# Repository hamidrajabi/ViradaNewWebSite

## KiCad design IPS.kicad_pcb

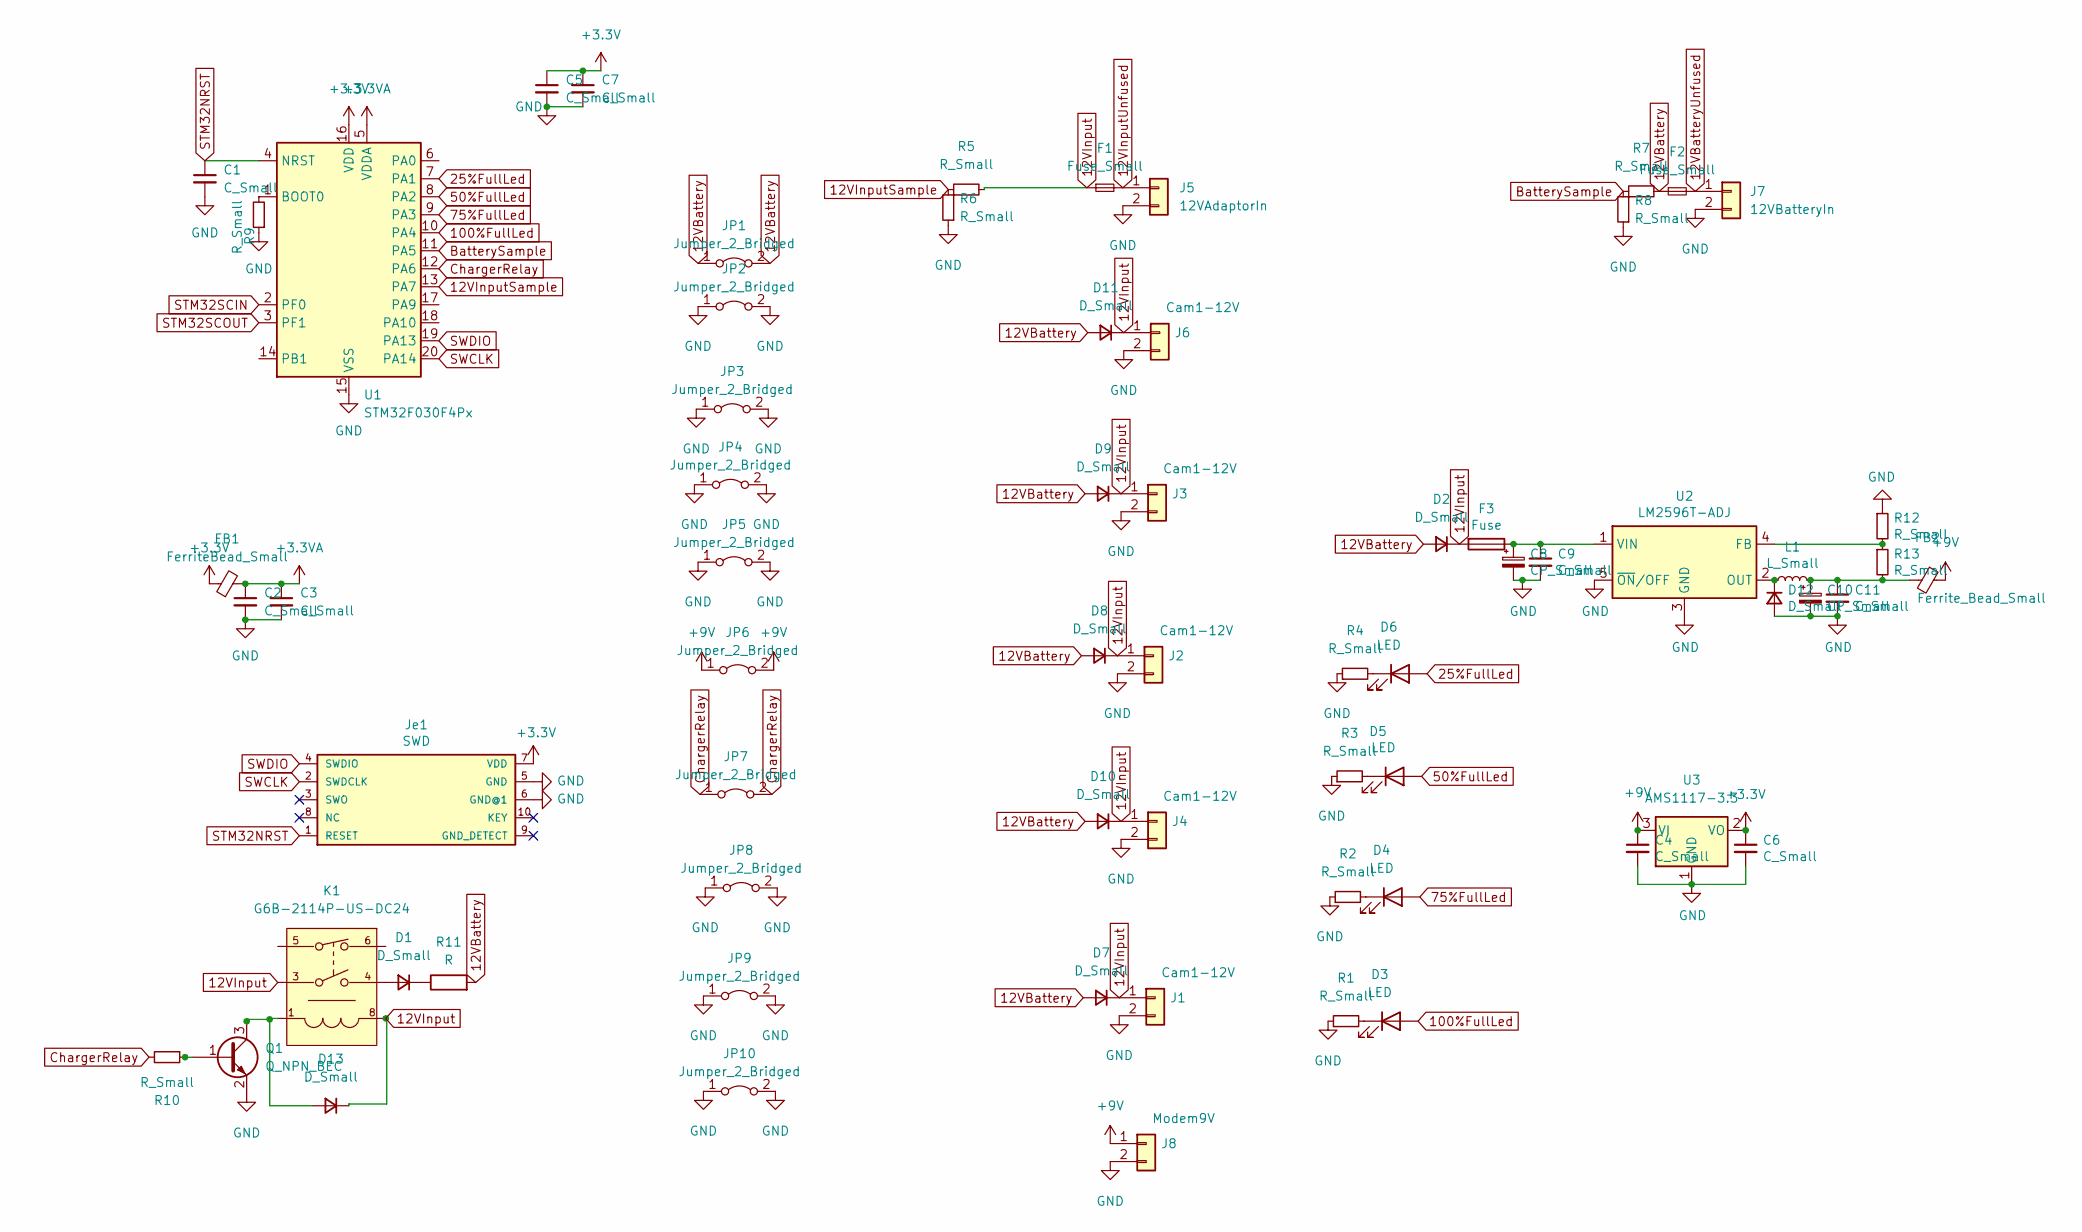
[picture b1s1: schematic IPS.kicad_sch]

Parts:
C1, C2, C3, C4, C5, C6, C7, C9, C11: C_Small; C_1206_3216Metric_Pad1.33x1.80mm_HandSolder
C8, C10: CP_Small; CP_Elec_10x10
D1, D2, D7, D8, D9, D10, D11, D12, D13: D_Small; D_SMA_Handsoldering
D3, D4, D5, D6: LED; LED_1206_3216Metric_Pad1.42x1.75mm_HandSolder
F1, F2: Fuse_Small; Fuse_1206_3216Metric_Pad1.42x1.75mm_HandSolder
F3: Fuse; Fuse_1206_3216Metric_Pad1.42x1.75mm_HandSolder
FB1: FerriteBead_Small; C_1206_3216Metric_Pad1.33x1.80mm_HandSolder
FB2: Ferrite_Bead_Small; C_1206_3216Metric_Pad1.33x1.80mm_HandSolder
J1, J2, J3, J4, J6: Cam1-12V; PhoenixContact_MSTBA_2,5_2-G_1x02_P5.00mm_Horizontal
J5: 12VAdaptorIn; PhoenixContact_MSTBA_2,5_2-G_1x02_P5.00mm_Horizontal
J7: 12VBatteryIn; PhoenixContact_MSTBA_2,5_2-G_1x02_P5.00mm_Horizontal
J8: Modem9V; PhoenixContact_MSTBA_2,5_2-G_1x02_P5.00mm_Horizontal
JP1, JP2, JP3, JP4, JP5, JP6, JP7, JP8, JP9, JP10: Jumper_2_Bridged; R_1206_3216Metric_Pad1.30x1.75mm_HandSolder
Je1: SWD; IDC-Header_2x05_P2.54mm_Vertical
K1: G6B-2114P-US-DC24; Omron-G6B-2114P-US-DC24-MFG; coil voltage 24V; current rating 5A; mouser part number 653-G6B-2114P-DC24; digikey description RELAY GEN PURPOSE DPST 5A 24V
L1: L_Small; L_12x12mm_H6mm
Q1: Q_NPN_BEC; SOT-23
R1, R2, R3, R4, R5, R6, R7, R8, R9, R10, R12, R13: R_Small; R_1206_3216Metric_Pad1.30x1.75mm_HandSolder
R11: R; R_Axial_DIN0207_L6.3mm_D2.5mm_P10.16mm_Horizontal
U1: STM32F030F4Px; TSSOP-20_4.4x6.5mm_P0.65mm
U2: LM2596T-ADJ; TO-263-5_TabPin3
U3: AMS1117-3.3; SOT-223-3_TabPin2

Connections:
12VBattery: D2.2 (A), D7.2 (A), D8.2 (A), D9.2 (A), D10.2 (A), D11.2 (A), F2.1, JP1.1 (A), JP1.2 (B), R7.2, R11.2
12VBatteryUnfused: F2.2, J7.1
12VInput: D2.1 (K), D7.1 (K), D8.1 (K), D9.1 (K), D10.1 (K), D11.1 (K), D13.1 (K), F1.1, F3.2, J1.1, J2.1, J3.1, J4.1, J6.1, K1.3, K1.8, R5.2
12VInputSample: R5.1, R6.2, U1.13 (PA7)
12VInputUnfused: F1.2, J5.1
25%FullLed: D6.2 (A), U1.7 (PA1)
50%FullLed: D5.2 (A), U1.8 (PA2)
75%FullLed: D4.2 (A), U1.9 (PA3)
100%FullLed: D3.2 (A), U1.10 (PA4)
+3.3VA: C2.1, C3.1, FB1.2, U1.5 (VDDA)
+3V3: C5.1, C6.1, C7.1, FB1.1, Je1.7 (VDD), U1.16 (VDD), U3.2 (VO)
+9V: C4.1, FB2.1, J8.1, JP6.1 (A), JP6.2 (B), U3.3 (VI)
BatterySample: R7.1, R8.2, U1.11 (PA5)
ChargerRelay: JP7.1 (A), JP7.2 (B), R10.2, U1.12 (PA6)
GND: C1.2, C2.2, C3.2, C4.2, C5.2, C6.2, C7.2, C8.2, C9.2, C10.2, C11.2, D12.2 (A), J1.2, J2.2, J3.2, J4.2, J5.2, J6.2, J7.2, J8.2, JP2.1 (A), JP2.2 (B), JP3.1 (A), JP3.2 (B), JP4.1 (A), JP4.2 (B), JP5.1 (A), JP5.2 (B), JP8.1 (A), JP8.2 (B), JP9.1 (A), JP9.2 (B), JP10.1 (A), JP10.2 (B), Je1.5 (GND), Je1.6 (GND@1), Q1.2 (E), R1.1, R2.1, R3.1, R4.1, R6.1, R8.1, R9.1, R12.1, U1.15 (VSS), U2.3 (GND), U2.5 (~ON/OFF), U3.1 (GND)
unnamed: C8.1, C9.1, F3.1, U2.1 (VIN)
unnamed: C10.1, C11.1, FB2.2, L1.2, R13.2
unnamed: D1.1 (K), R11.1
unnamed: D1.2 (A), K1.4
unnamed: D3.1 (K), R1.2
unnamed: D4.1 (K), R2.2
unnamed: D5.1 (K), R3.2
unnamed: D6.1 (K), R4.2
unnamed: D12.1 (K), L1.1, U2.2 (OUT)
unnamed: D13.2 (A), K1.1, Q1.3 (C)
unnamed: R9.2, U1.1 (BOOT0)
unnamed: Q1.1 (B), R10.1
unnamed: R12.2, R13.1, U2.4 (FB)
STM32NRST: C1.1, Je1.1 (RESET), U1.4 (NRST)
STM32SCIN: U1.2 (PF0)
STM32SCOUT: U1.3 (PF1)
SWCLK: Je1.2 (SWDCLK), U1.20 (PA14)
SWDIO: Je1.4 (SWDIO), U1.19 (PA13)

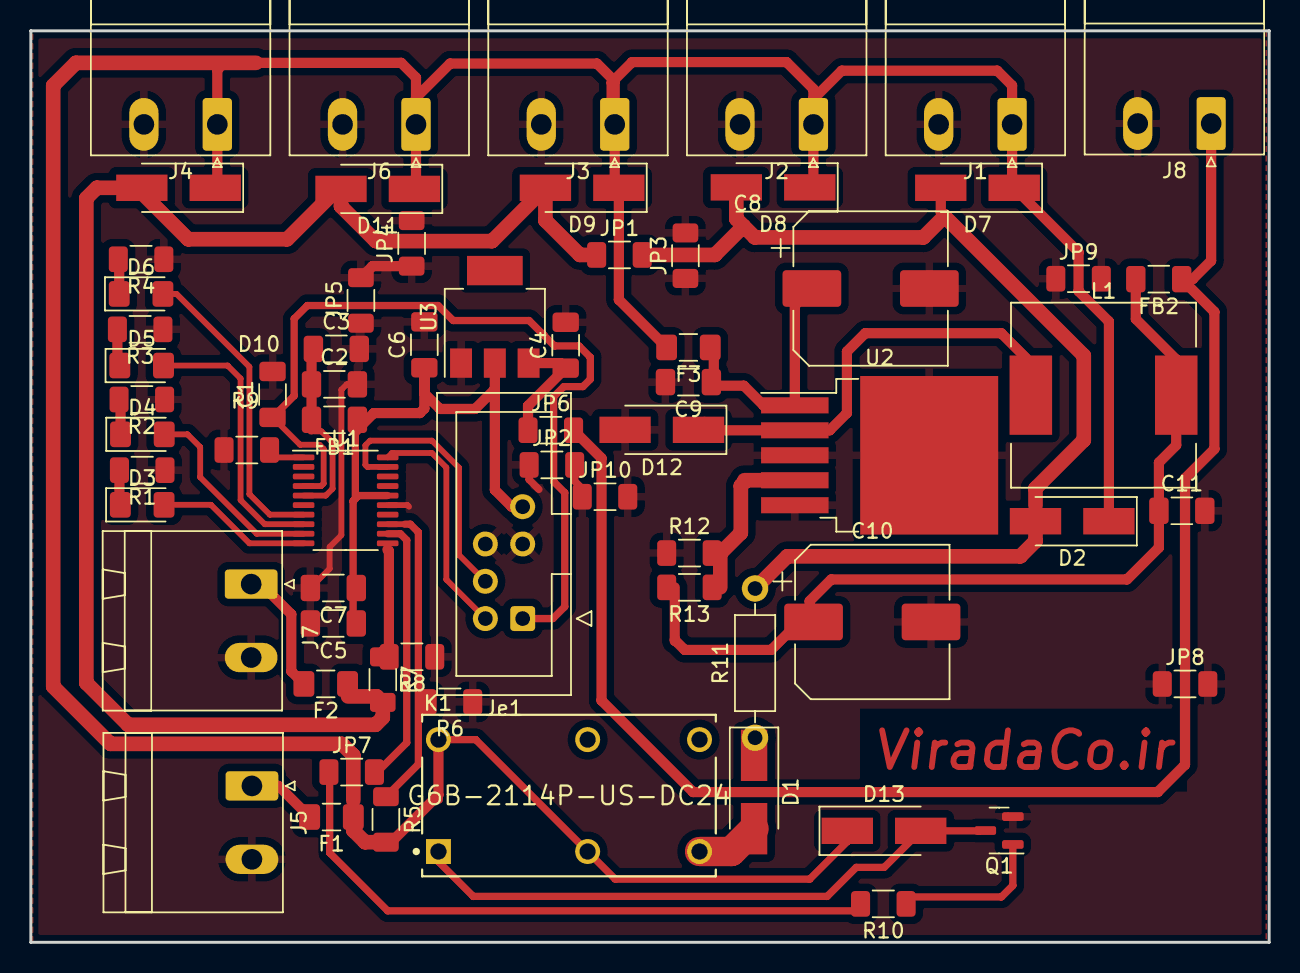
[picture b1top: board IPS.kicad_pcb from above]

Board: 2 copper layers, 84.3 x 62.1 mm, 67 parts (0 on the bottom side), 31 nets.

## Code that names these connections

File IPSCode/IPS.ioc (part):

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Mcu.Name=STM32F030F4Px
Mcu.Package=TSSOP20
Mcu.UserName=STM32F030F4Px
PA1.GPIOParameters=PinState,GPIO_Label
PA1.GPIO_Label=FullChargedLed
PA1.PinState=GPIO_PIN_RESET
PA1.Signal=GPIO_Output
PA13.Mode=Serial_Wire
PA13.Signal=SYS_SWDIO
PA14.Mode=Serial_Wire
PA14.Signal=SYS_SWCLK
PA2.GPIOParameters=GPIO_Label
PA2.GPIO_Label=ThreeQuartersFilledLed
PA2.Signal=GPIO_Output
PA3.GPIOParameters=GPIO_Label
PA3.GPIO_Label=HalfFilledLed
PA3.Signal=GPIO_Output
PA4.GPIOParameters=PinState,GPIO_Label
PA4.GPIO_Label=QuarterFilledLed
PA4.PinState=GPIO_PIN_RESET
PA4.Signal=GPIO_Output
PA5.Mode=IN5
PA5.Signal=ADC_IN5
PA6.GPIOParameters=GPIO_Label
PA6.GPIO_Label=ChargeRelay
PA6.Signal=GPIO_Output
PA7.Mode=IN7
PA7.Signal=ADC_IN7
RCC.SYSCLKFreq_VALUE=16000000
RCC.SYSCLKSource=RCC_SYSCLKSOURCE_PLLCLK
board=custom

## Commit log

2024-02-28 added new files
2024-02-28 removed all
